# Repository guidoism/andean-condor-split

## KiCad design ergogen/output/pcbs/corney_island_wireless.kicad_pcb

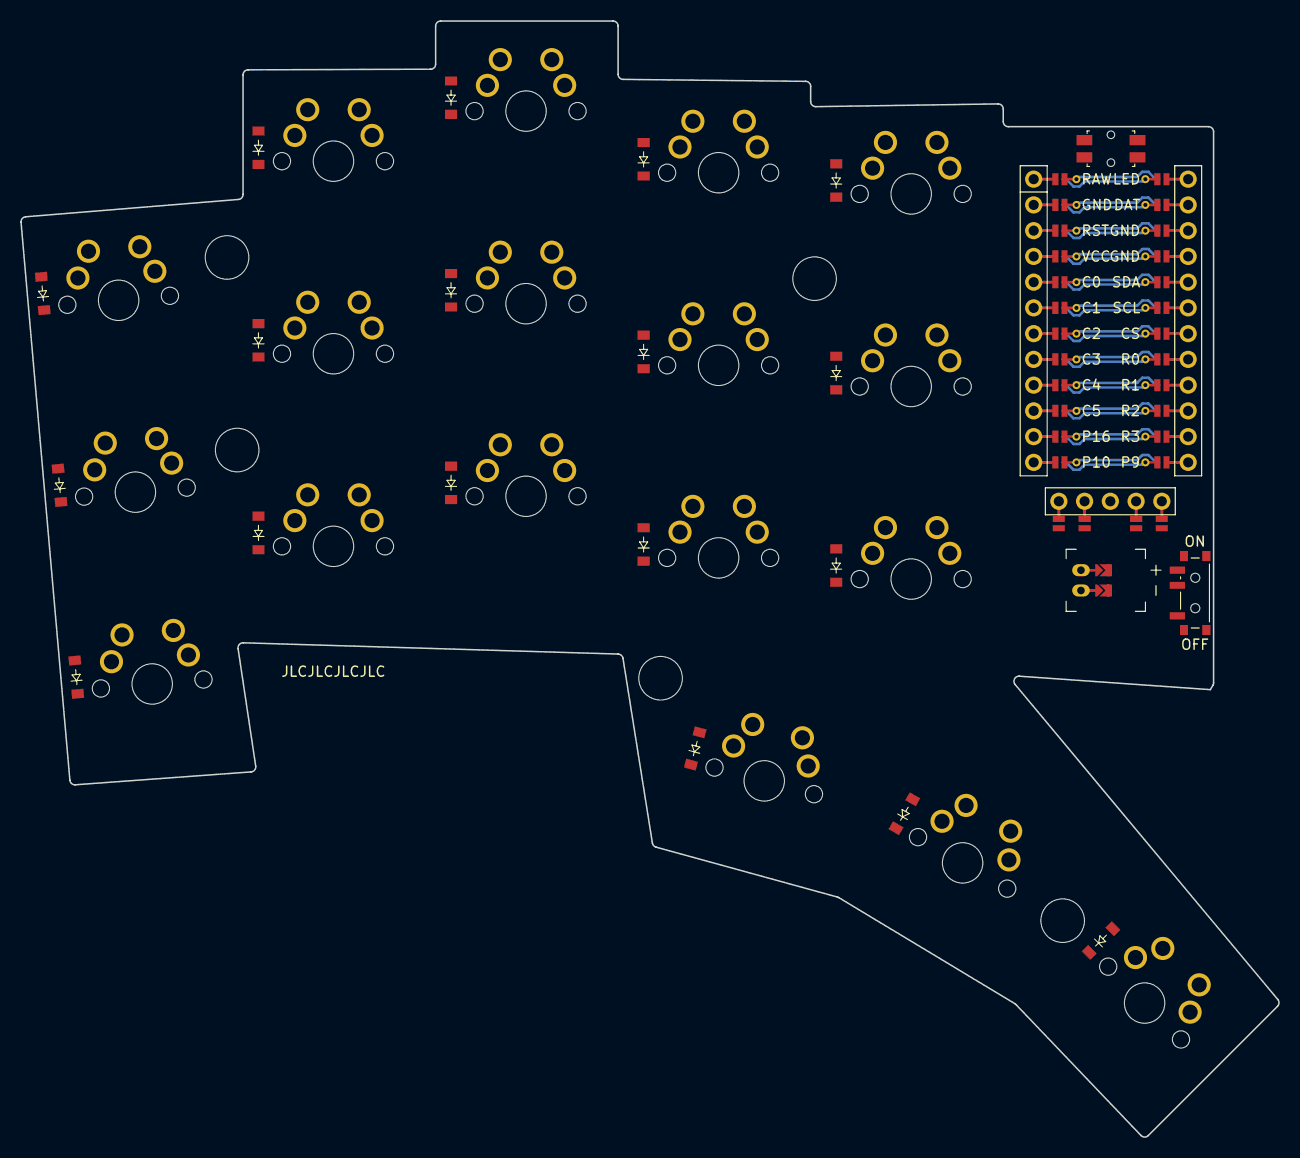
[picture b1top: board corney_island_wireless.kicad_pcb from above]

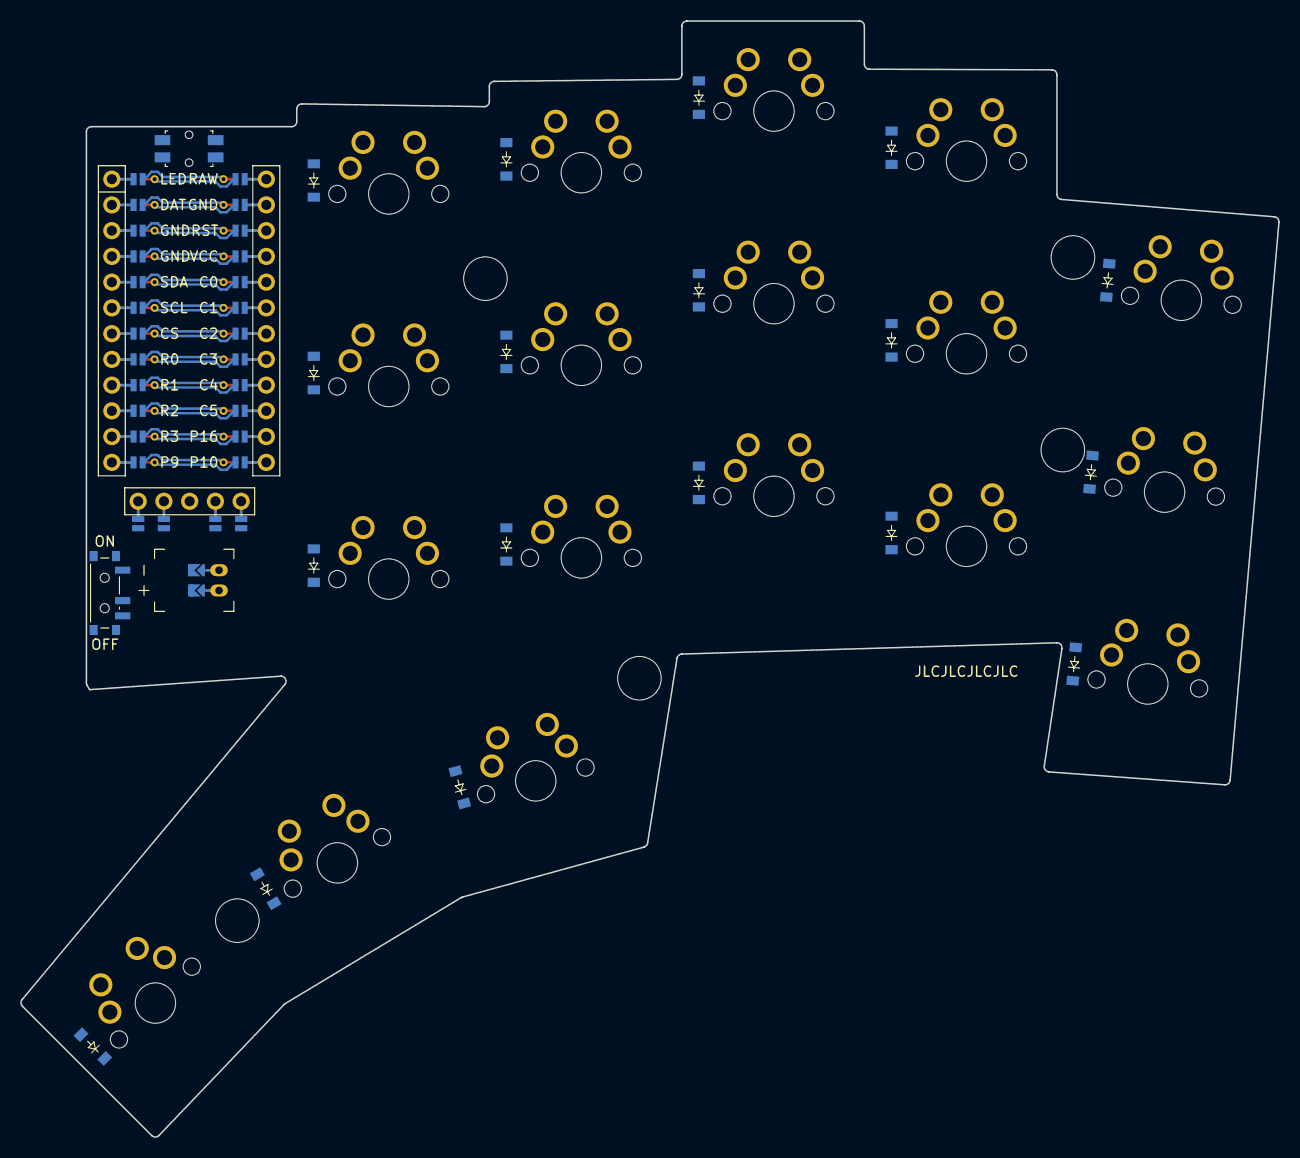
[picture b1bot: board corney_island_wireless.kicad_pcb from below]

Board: 2 copper layers, 124.1 x 110.1 mm, 64 parts (18 on the bottom side), 53 nets.

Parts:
D1, D2, D3, D4, D5, D6, D7, D8, D9, D10, D11, D12, D13, D14, D15, D16, D17, D18, D19, D20, D21, D22, D23, D24, D25, D26, D27, D28, D29, D30, D31, D32, D33, D34, D35, D36: diode_tht_sod123
DISP1: display_nice_view
JST1: battery_connector_jst_ph_2
MCU1: mcu_nice_nano
MH1, MH2, MH3, MH4, MH5: mounting_hole_npth
PWR1: power_switch; power_switch_smd_side
RST1: reset_button_smd_side
S1, S2, S3, S4, S5, S6, S7, S8, S9, S10, S11, S12, S13, S14, S15, S16, S17, S18: MX

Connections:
BAT_P: JST1.1, PWR1.1, PWR1.3
C1: MCU1.119, S1.1, S2.1, S3.1
C2: MCU1.118, S4.1, S5.1, S6.1
C3: MCU1.117, S7.1, S8.1, S9.1, S16.1
C4: MCU1.116, S10.1, S11.1, S12.1, S17.1
C5: MCU1.115, S13.1, S14.1, S15.1, S18.1
CS: DISP1.10, DISP1.20, MCU1.7
DISP1_1: DISP1.1, DISP1.14, DISP1.27
DISP1_2: DISP1.2, DISP1.15, DISP1.26
DISP1_4: DISP1.4, DISP1.16, DISP1.25
DISP1_5: DISP1.5, DISP1.17, DISP1.24
GND: DISP1.11, DISP1.21, JST1.2, MCU1.3, MCU1.4, MCU1.123, RST1.1, RST1.3
JST1_1: JST1.11, JST1.21, JST1.31
JST1_2: JST1.12, JST1.22, JST1.32
MCU1_1: MCU1.1, MCU1.24
MCU1_2: MCU1.2, MCU1.23
MCU1_3: MCU1.3, MCU1.22
MCU1_4: MCU1.4, MCU1.21
MCU1_5: MCU1.5, MCU1.20
MCU1_6: MCU1.6, MCU1.19
MCU1_7: MCU1.7, MCU1.18
MCU1_8: MCU1.8, MCU1.17
MCU1_9: MCU1.9, MCU1.16
MCU1_10: MCU1.10, MCU1.15
MCU1_11: MCU1.11, MCU1.14
MCU1_12: MCU1.12, MCU1.13
R0: D3.1, D6.1, D9.1, D12.1, D15.1, D21.1, D24.1, D27.1, D30.1, D33.1, MCU1.8
R1: D2.1, D5.1, D8.1, D11.1, D14.1, D20.1, D23.1, D26.1, D29.1, D32.1, MCU1.9
R2: D1.1, D4.1, D7.1, D10.1, D13.1, D19.1, D22.1, D25.1, D28.1, D31.1, MCU1.10
R3: D16.1, D17.1, D18.1, D34.1, D35.1, D36.1, MCU1.11
RAW: MCU1.124, PWR1.2
RST: MCU1.122, RST1.2, RST1.4
SCL: DISP1.12, DISP1.22, MCU1.6
SDA: DISP1.13, DISP1.23, MCU1.5
VCC: DISP1.3, MCU1.121
far_home: D18.2, D36.2, S18.2
index_bottom: D10.2, D28.2, S10.2
index_home: D11.2, D29.2, S11.2
index_top: D12.2, D30.2, S12.2
inner_bottom: D13.2, D31.2, S13.2
inner_home: D14.2, D32.2, S14.2
inner_top: D15.2, D33.2, S15.2
mid_home: D17.2, D35.2, S17.2
middle_bottom: D7.2, D25.2, S7.2
middle_home: D8.2, D26.2, S8.2
middle_top: D9.2, D27.2, S9.2
near_home: D16.2, D34.2, S16.2
pinky_bottom: D1.2, D19.2, S1.2
pinky_home: D2.2, D20.2, S2.2
pinky_top: D3.2, D21.2, S3.2
ring_bottom: D4.2, D22.2, S4.2
ring_home: D5.2, D23.2, S5.2
ring_top: D6.2, D24.2, S6.2

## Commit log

2024-03-14 Checkpoint
2024-03-15 Removed LEDs
2024-03-15 Switched columns for thumb keys
2024-03-15 Disable hotswap
2024-04-30 Removed outer column
2024-04-30 Changed stagger to be like karia
2024-04-30 Added splay to pinky
2024-04-30 Changed thumb key back to 1u
2024-04-30 Changed thumb splay
2024-04-30 Moved screws back onto board
2024-04-30 Moved screws around a bit
2024-04-30 Typo
2024-04-30 Tweak shape
